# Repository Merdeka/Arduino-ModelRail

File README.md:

# Code for all kinds of LocoNet devices using an Arduino

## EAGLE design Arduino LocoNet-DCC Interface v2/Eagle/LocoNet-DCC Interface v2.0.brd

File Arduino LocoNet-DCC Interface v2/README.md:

# Arduino Nano LocoNet & DCC Interface v2

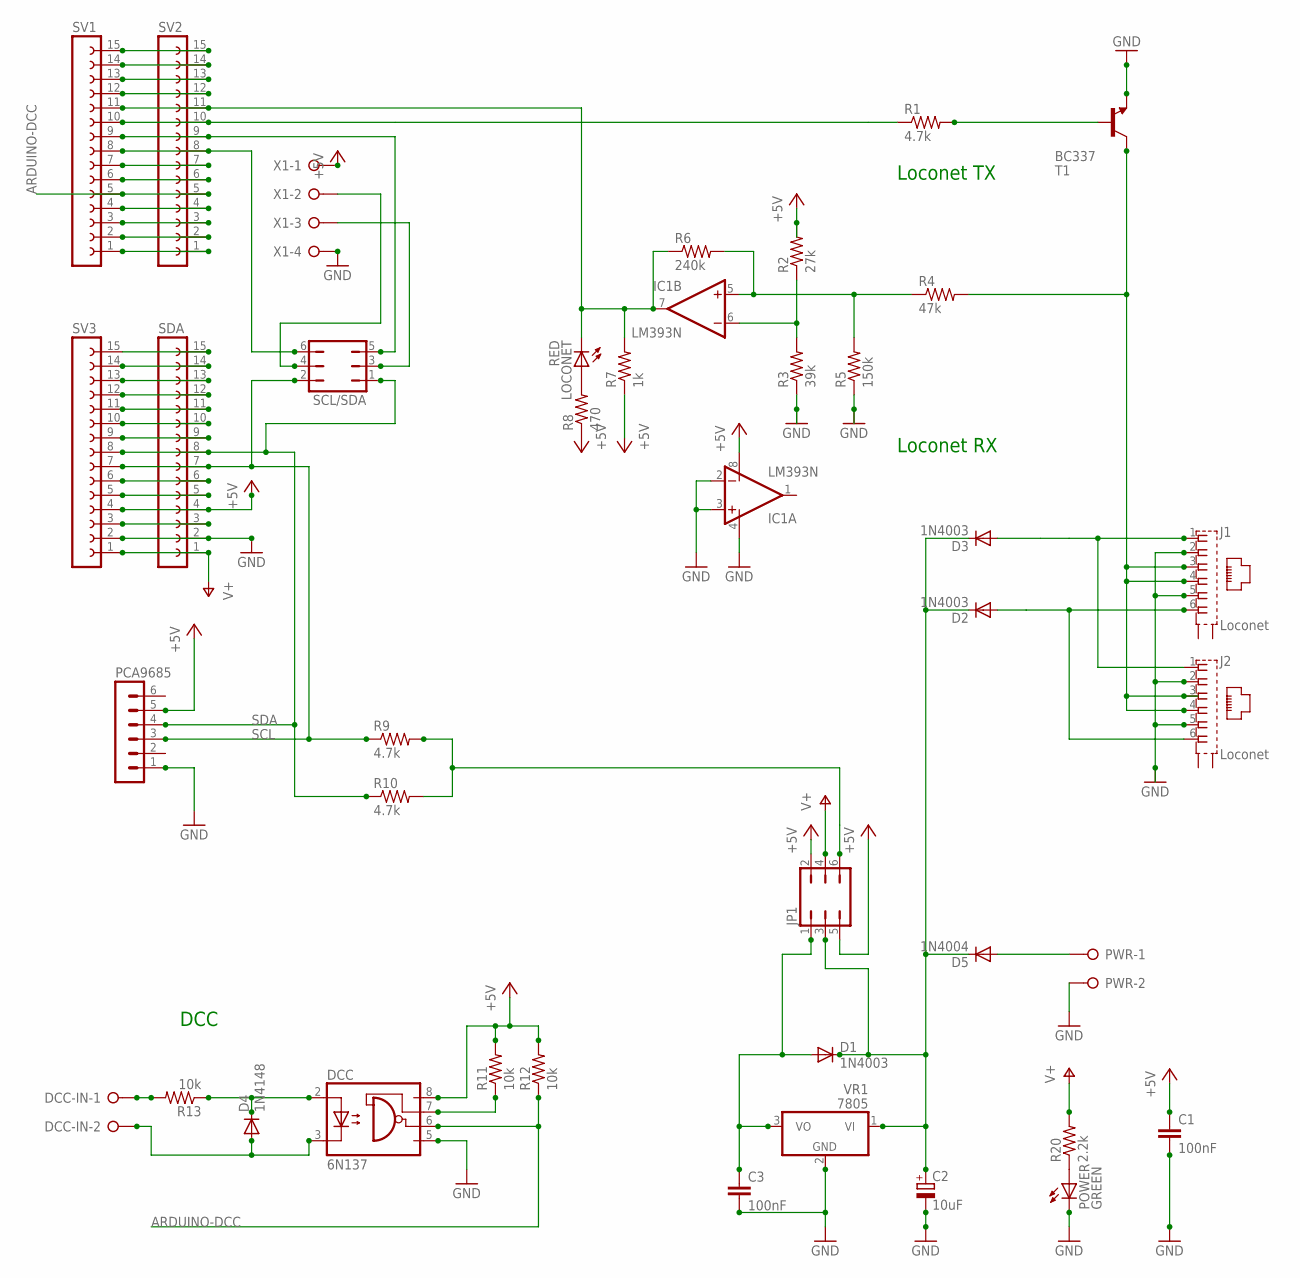
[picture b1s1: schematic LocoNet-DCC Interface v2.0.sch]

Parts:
C1, C3: 100nF; C025_050-025X075
C2: 10uF; E2,5-6
D1, D2, D3: 1N4003; DO41-10
D4: 1N4148; DO35-7
D5: 1N4004; DO41-10
DCC: 6N137; DIL08
DCC-IN: W237-02P; W237-132
IC1: LM393N; DIL08
J1, J2: Loconet; 555140-1
JP1: JP3Q
LOCONET: RED; LED3MM
PCA9685: MA06-1
POWER: GREEN; LED3MM
PWR: W237-02P; W237-132
R1, R9, R10: 4.7k; AXIAL-0.3
R2: 27k; AXIAL-0.3
R3: 39k; AXIAL-0.3
R4: 47k; AXIAL-0.3
R5: 150k; AXIAL-0.3
R6: 240k; AXIAL-0.3
R7: 1k; AXIAL-0.3
R8: 470; AXIAL-0.3
R11, R12, R13: 10k; AXIAL-0.3
R20: 2.2k; AXIAL-0.3
SCL/SDA: JP3Q
SDA: FE15-1NOTEXT; FE15
SV1, SV2, SV3: FE15-1NOTEXT; FE15
T1: BC337; TO92
VR1: 7805; TO220V
X1: W237-04P; W237-4P

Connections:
3V3: SDA.14, SV3.14
+5V: C1.1, DCC.8 (VCC), IC1.8 (V+), JP1.2, JP1.5, PCA9685.5, R2.P$2 (2), R7.P$1 (1), R8.P$1 (1), R11.P$2 (2), R12.P$2 (2), SDA.4, SV3.4, X1.1
A0: SDA.12, SV3.12
A1: SDA.11, SV3.11
A2: SDA.10, SV3.10
A3: SDA.9, SV3.9
A6: SDA.6, SV3.6
A7: SDA.5, SV3.5
ARDUINO-DCC: DCC.6 (VO), R12.P$1 (1), SV1.5, SV2.5
AREF: SDA.13, SV3.13
GND: C1.2, C2.-, C3.2, DCC.5 (GND), IC1.2 (-IN), IC1.3 (+IN), IC1.4 (V-), J1.2, J1.5, J2.2, J2.5, PCA9685.1, POWER.K (C), PWR.2, R3.P$1 (1), R5.P$1 (1), SDA.2, SV3.2, T1.1 (E), VR1.2 (GND), X1.4
I2C_PULLUP: JP1.6, R9.P$2 (2), R10.P$2 (2)
L-RX: IC1.7 (OUT), LOCONET.K (C), R6.P$1 (1), R7.P$2 (2), SV1.11, SV2.11
L-TX: R1.P$1 (1), SV1.10, SV2.10
LOCONET-SIGNAL: J1.3, J1.4, J2.3, J2.4, R4.P$2 (2), T1.3 (C)
unnamed: D5.A, PWR.1
unnamed: POWER.A, R20.P$1 (1)
unnamed: LOCONET.A, R8.P$2 (2)
unnamed: R1.P$2 (2), T1.2 (B)
unnamed: IC1.6 (-IN), R2.P$1 (1), R3.P$2 (2)
unnamed: IC1.5 (+IN), R4.P$1 (1), R5.P$2 (2), R6.P$2 (2)
unnamed: SDA.3, SV3.3
unnamed: SV1.4, SV2.4
unnamed: D4.C, DCC.2 (A), R13.P$1 (1)
unnamed: D4.A, DCC.3 (C), DCC-IN.2
unnamed: DCC.7 (VE), R11.P$1 (1)
unnamed: DCC-IN.1, R13.P$2 (2)
PIN3: SV1.6, SV2.6
PIN4: SV1.7, SV2.7
PIN5: SCL/SDA.6, SV1.8, SV2.8
PIN6: SCL/SDA.5, SV1.9, SV2.9
PIN9: SV1.12, SV2.12
PIN10: SV1.13, SV2.13
PIN11: SV1.14, SV2.14
PIN12: SV1.15, SV2.15
PIN13: SDA.15, SV3.15
RAILSYNC-A: D3.A, J1.1, J2.1
RAILSYNC-B: D2.A, J1.6, J2.6
RAILSYNC-VIN: C2.+, D1.C, D2.C, D3.C, D5.C, JP1.3, VR1.1 (VI)
RESET: SV1.3, SV2.3
RXD: SV1.2, SV2.2
SCL: PCA9685.3, R9.P$1 (1), SCL/SDA.2, SDA.7, SV3.7
SDA: PCA9685.4, R10.P$1 (1), SCL/SDA.1, SDA.8, SV3.8
TXD: SV1.1, SV2.1
V-OUT: C3.1, D1.A, JP1.1, VR1.3 (VO)
VIN: JP1.4, R20.P$2 (2), SDA.1, SV3.1
X1-SCL/D5: SCL/SDA.4, X1.2
X1-SDA/D6: SCL/SDA.3, X1.3

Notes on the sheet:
Loconet RX
Loconet TX
DCC

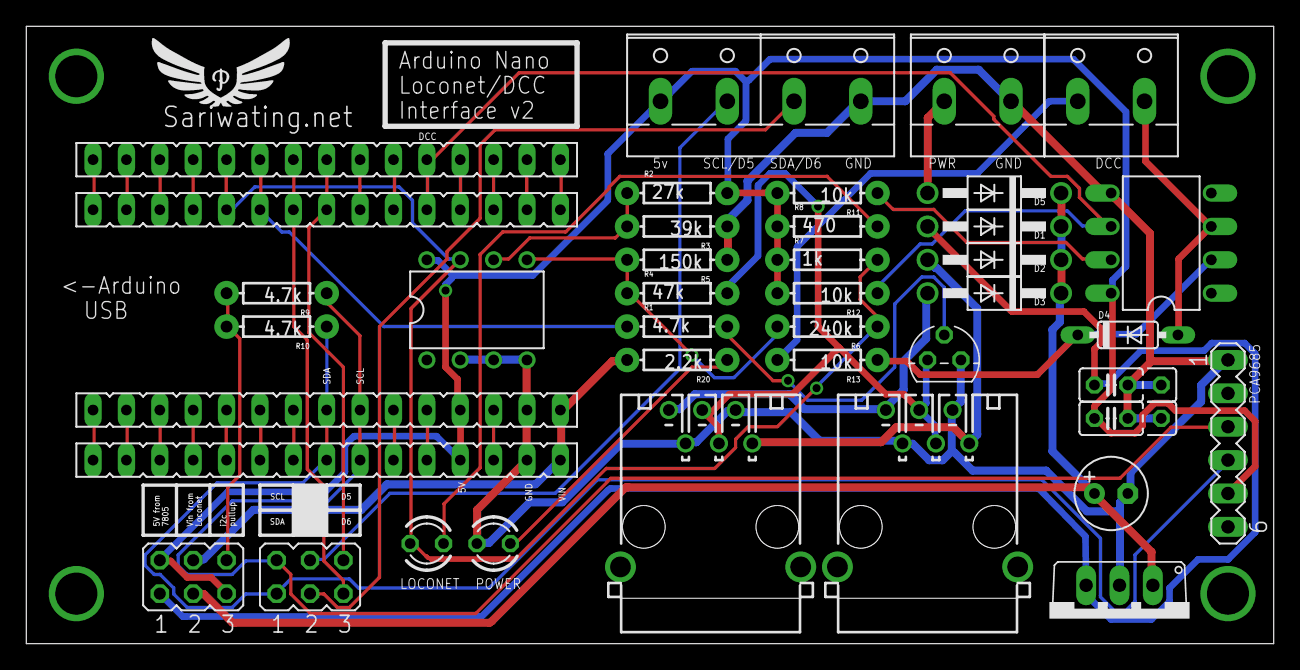
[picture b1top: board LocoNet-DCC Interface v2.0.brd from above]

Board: 2 copper layers, 94.9 x 47.0 mm, 40 parts (0 on the bottom side), 48 nets.

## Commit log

2015-12-09 added README.md
2015-12-09 Cleanup
2015-12-10 Add LocoNet UDP Sketch
2015-12-10 Code Cleanup
2015-12-10 Bugfix
2015-12-10 Store Button State in EEPROM and send on power up
2015-12-11 Small update
2015-12-11 Adjusted the LED PWM. Where way to bright
2015-12-13 Added 2 WS2812b Signals
2015-12-28 Add Loconet WS2812b
2016-01-02 Bug fixes and simplification
    Switched to Bounce2 library to bugfix the buttons
    Used const for pin definitions
    Simplified some parts
2016-01-03 Small Typo and added Loconet Github
2016-02-04 Small Change
2016-02-04 Initial Commit
    Needs Cleanup
2017-10-17 PCD Schematics
    PCD Schematics
2017-10-17 Add README.md
    Add README.md
2017-11-13 First Commit
    First Commit
2017-11-13 Name Change
    Name Change
2018-02-21 Manual Update

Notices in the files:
parts and their libraries:
SparkFun-Resistors: Licensing: Creative Commons ShareAlike 4.0 International - https://creativecommons.org/licenses/by-sa/4.0
